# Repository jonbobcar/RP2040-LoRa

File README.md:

# RP2040 LoRa
 RP2040 based board with a LoRa radio

KiCad files are made with KiCad v7.

Care should be used when purchasing BMS to choose one that will auto-start. There are SKUs of this BMS that will only start if external power is provided and then removed. I have chosen AP9101CAK6-ANTRG1, which is an auto-start version.

This board is mostly tested. Files on `main` should be used with caution, you may need to do some debugging.

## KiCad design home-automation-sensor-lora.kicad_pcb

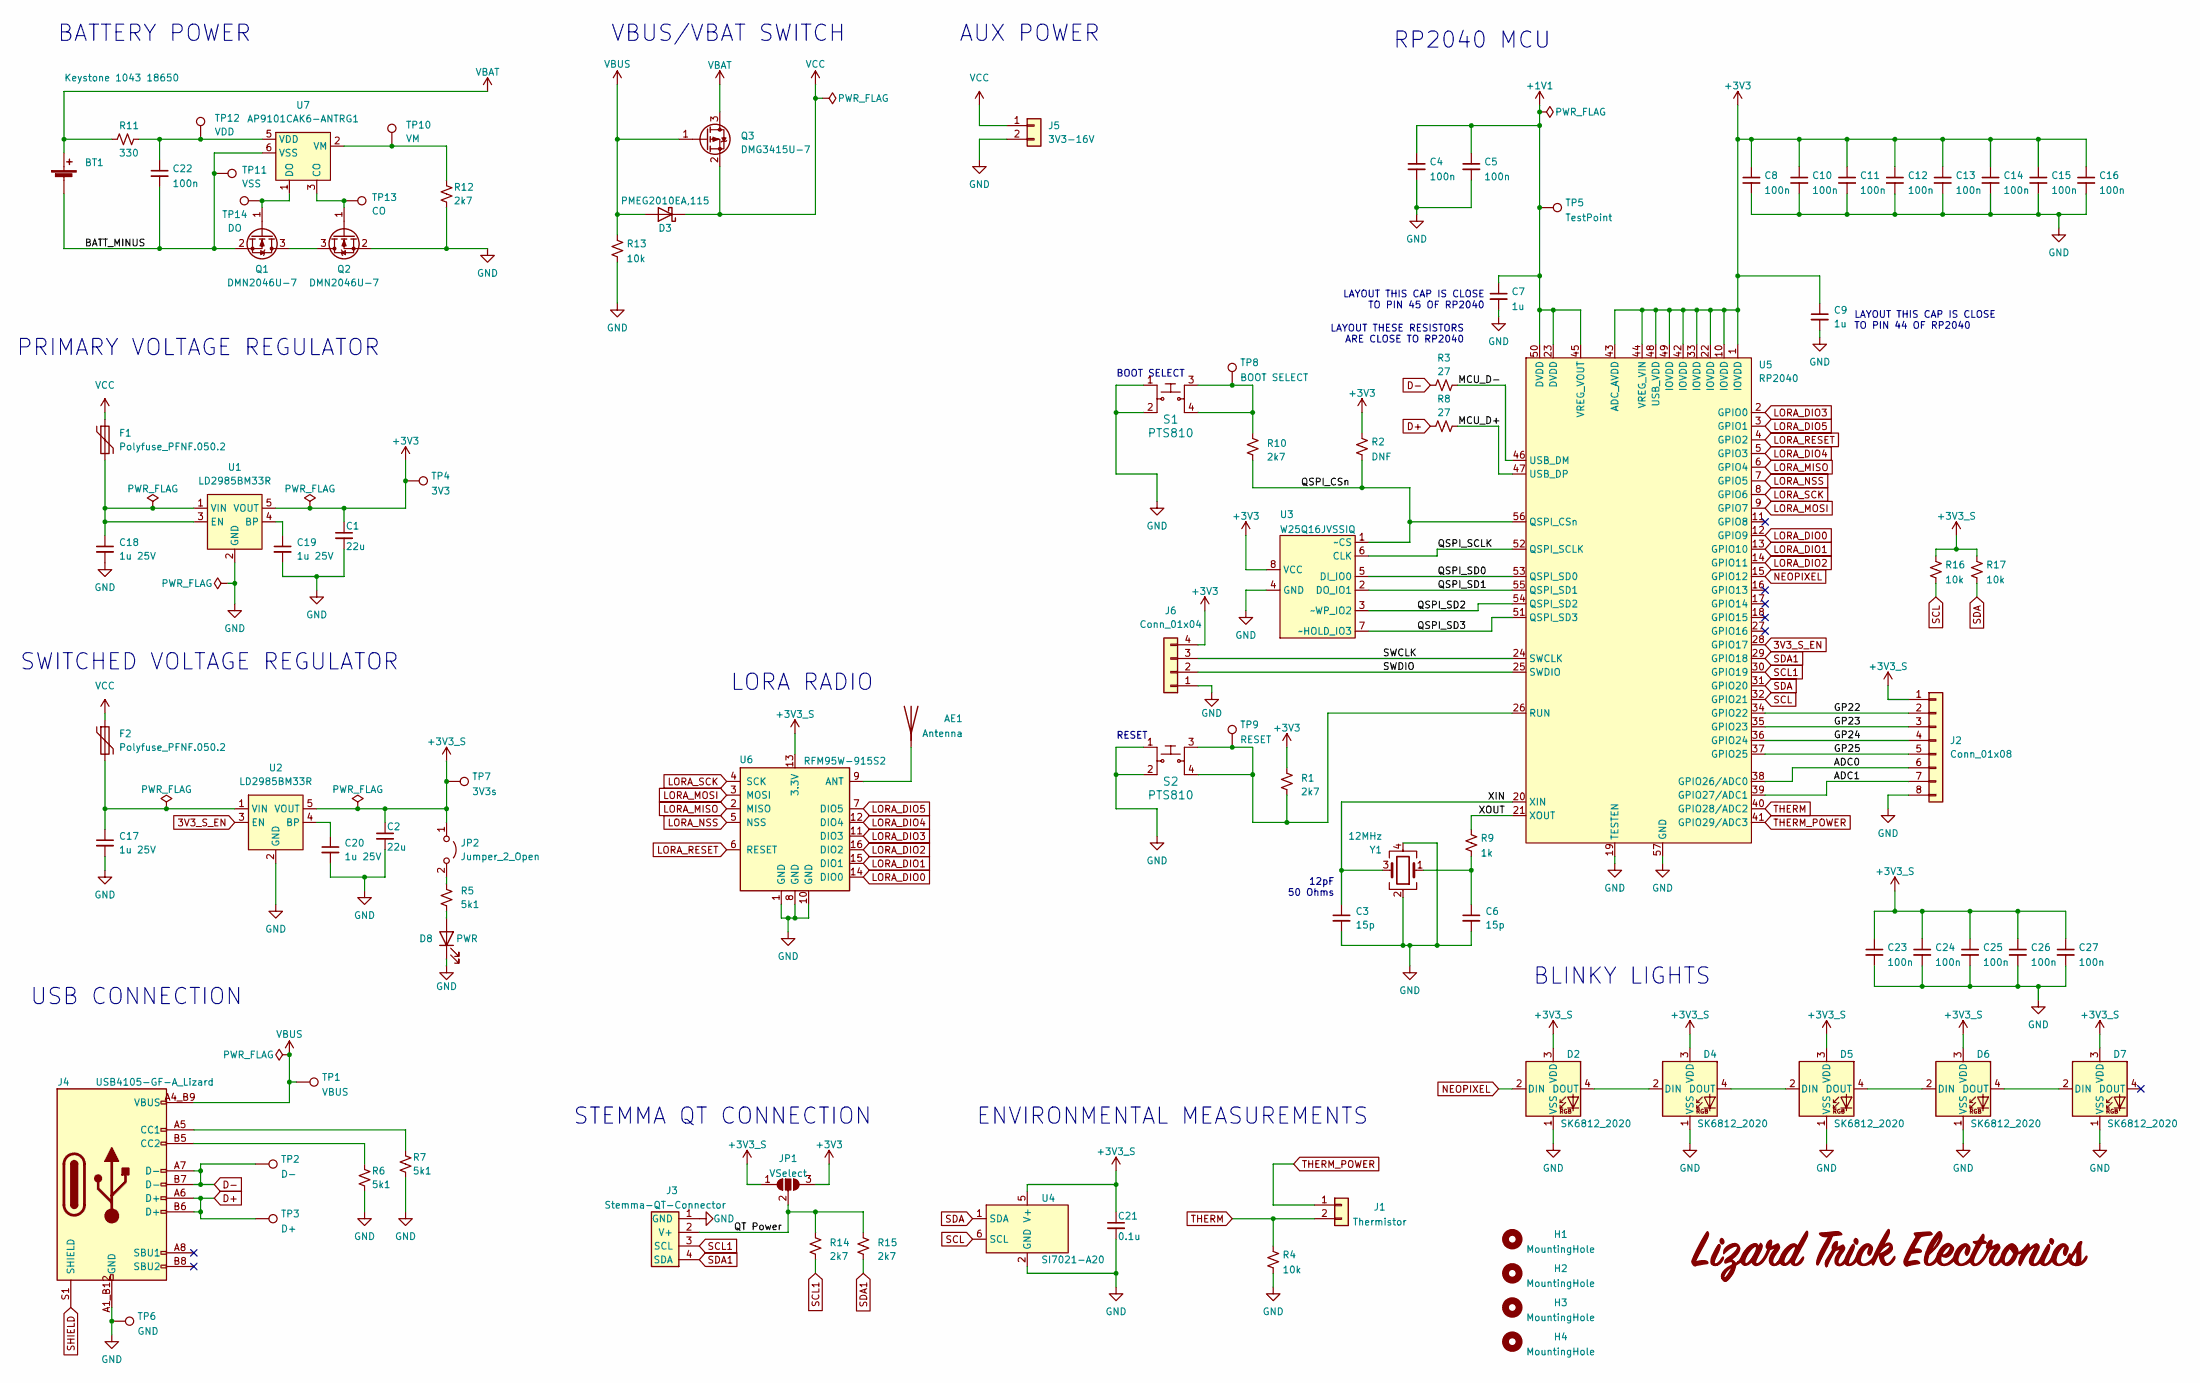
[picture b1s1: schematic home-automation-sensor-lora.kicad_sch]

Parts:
AE1: Antenna; Spring_Antenna_1.0_Drill
BT1: Keystone 1043 18650
C1, C2: 22u; C_0603_Lizard
C3, C6: 15p; C_0603_Lizard
C4, C5, C8, C10, C11, C12, C13, C14, C15, C16, C22, C23, C24, C25, C26, C27: 100n; C_0603_Lizard
C7, C9: 1u; C_0603_Lizard
C17, C18, C19, C20: 1u 25V; C_0603_Lizard
C21: 0.1u; C_0603_Lizard
D2, D4, D5, D6, D7: SK6812_2020; SK6812 2020
D3: PMEG2010EA,115; D_SOD-323
D8: PWR; LED-0805-Lizard
F1, F2: Polyfuse_PFNF.050.2; R_1206_3216Metric
G1: LOGO; Lizard Text Logo
H1, H2, H3, H4: MountingHole; Lizard_MountingHole_3.5mm
J1: Thermistor; PinHeader_1x02_P2.54mm_Vertical
J2: Conn_01x08; Prototype Area 8x8
J3: Stemma-QT-Connector; STEMMA-QT-CONNECTOR
J4: USB4105-GF-A_Lizard; GCT_USB4105-GF-A
J5: 3V3-16V; PinHeader_1x02_P2.54mm_Vertical
J6: Conn_01x04; PinHeader_1x04_P2.54mm_Vertical
JP1: VSelect; SolderJumper-3_P2.0mm_Open_TrianglePad1.0x1.5mm
JP2: Jumper_2_Open; Pin Jumper lizard
Q1, Q2: DMN2046U-7; SOT-23
Q3: DMG3415U-7; SOT-23
R1, R10, R12, R14, R15: 2k7; R_0603_Lizard
R2: DNF; R_0603_Lizard
R3, R8: 27; R_0603_Lizard
R4, R13, R16, R17: 10k; R_0603_Lizard
R5, R6, R7: 5k1; R_0603_Lizard
R9: 1k; R_0603_Lizard
R11: 330; R_0603_Lizard
S1, S2: PTS810; PTS_180_Tactile_Switch
TP1: VBUS; TestPoint_THTPad_1.0x1.0mm_Drill0.5mm
TP2: D-; TestPoint_THTPad_1.0x1.0mm_Drill0.5mm
TP3: D+; TestPoint_THTPad_1.0x1.0mm_Drill0.5mm
TP4: 3V3; TestPoint_THTPad_1.0x1.0mm_Drill0.5mm
TP5: TestPoint; TestPoint_THTPad_1.0x1.0mm_Drill0.5mm
TP6: GND; TestPoint_THTPad_1.0x1.0mm_Drill0.5mm
TP7: 3V3s; TestPoint_THTPad_1.0x1.0mm_Drill0.5mm
TP8: BOOT SELECT; TestPoint_THTPad_1.0x1.0mm_Drill0.5mm
TP9: RESET; TestPoint_THTPad_1.0x1.0mm_Drill0.5mm
TP10: VM; TestPoint_THTPad_1.0x1.0mm_Drill0.5mm-Lizard
TP11: VSS; TestPoint_THTPad_1.0x1.0mm_Drill0.5mm-Lizard
TP12: VDD; TestPoint_THTPad_1.0x1.0mm_Drill0.5mm-Lizard
TP13: CO; TestPoint_THTPad_1.0x1.0mm_Drill0.5mm-Lizard
TP14: DO; TestPoint_THTPad_1.0x1.0mm_Drill0.5mm-Lizard
U1, U2: LD2985BM33R; SOT-23-5
U3: W25Q16JVSSIQ; SOIC-8_5.275x5.275mm_P1.27mm
U4: SI7021-A20
U5: RP2040; RP2040_QFN-56
U6: RFM95W-915S2; XCVR_RFM95W-915S2
U7: AP9101CAK6-ANTRG1; SOT-23-6
Y1: 12MHz; Crystal_SMD_3225-4Pin_3.2x2.5mm

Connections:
3V3_S_EN: U2.3 (EN), U5.28 (GPIO17)
+1V1: C4.1, C5.1, C7.1, TP5.1, U5.23 (DVDD), U5.45 (VREG_VOUT), U5.50 (DVDD)
+3V3: C1.1, C8.1, C9.1, C10.1, C11.1, C12.1, C13.1, C14.1, C15.1, C16.1, J6.4, JP1.3 (B), R1.1, R2.1, TP4.1, U1.5 (VOUT), U3.8 (VCC), U5.1 (IOVDD), U5.10 (IOVDD), U5.22 (IOVDD), U5.33 (IOVDD), U5.42 (IOVDD), U5.43 (ADC_AVDD), U5.44 (VREG_VIN), U5.48 (USB_VDD), U5.49 (IOVDD)
+3V3_S: C2.1, C21.1, C23.1, C24.1, C25.1, C26.1, C27.1, D2.3 (VDD), D4.3 (VDD), D5.3 (VDD), D6.3 (VDD), D7.3 (VDD), J2.1, JP1.1 (A), JP2.1 (A), R16.1, R17.1, TP7.1, U2.5 (VOUT), U4.5 (V+), U6.13 (3.3V)
/ADC0: J2.6, U5.38 (GPIO26/ADC0)
/ADC1: J2.7, U5.39 (GPIO27/ADC1)
/BATT_MINUS: BT1.1 (-), C22.2, Q1.2 (S), TP11.1, U7.6 (VSS)
/GP22: J2.2, U5.34 (GPIO22)
/GP23: J2.3, U5.35 (GPIO23)
/GP24: J2.4, U5.36 (GPIO24)
/GP25: J2.5, U5.37 (GPIO25)
/MCU_D+: R8.2, U5.47 (USB_DP)
/MCU_D-: R3.2, U5.46 (USB_DM)
/QSPI_CSn: R2.2, R10.2, U3.1 (~CS), U5.56 (QSPI_CSn)
/QSPI_SCLK: U3.6 (CLK), U5.52 (QSPI_SCLK)
/QSPI_SD0: U3.5 (DI_IO0), U5.53 (QSPI_SD0)
/QSPI_SD1: U3.2 (DO_IO1), U5.55 (QSPI_SD1)
/QSPI_SD2: U3.3 (~WP_IO2), U5.54 (QSPI_SD2)
/QSPI_SD3: U3.7 (~HOLD_IO3), U5.51 (QSPI_SD3)
/QT Power: J3.2 (V+), JP1.2 (C), R14.1, R15.1
/SWCLK: J6.3, U5.24 (SWCLK)
/SWDIO: J6.2, U5.25 (SWDIO)
/XIN: C3.1, U5.20 (XIN), Y1.3
/XOUT: R9.1, U5.21 (XOUT)
D+: J4.A6 (D+), J4.B6 (D+), R8.1, TP3.1
D-: J4.A7 (D-), J4.B7 (D-), R3.1, TP2.1
GND: C1.2, C2.2, C3.2, C4.2, C5.2, C6.2, C7.2, C8.2, C9.2, C10.2, C11.2, C12.2, C13.2, C14.2, C15.2, C16.2, C17.2, C18.2, C19.2, C20.2, C21.2, C23.2, C24.2, C25.2, C26.2, C27.2, D2.1 (VSS), D4.1 (VSS), D5.1 (VSS), D6.1 (VSS), D7.1 (VSS), D8.1 (K), J2.8, J3.1 (GND), J4.A1_B12 (GND), J4.B1_A12 (GND), J5.2, J6.1, Q2.2 (S), R4.2, R6.2, R7.2, R12.2, R13.2, S1.1, S1.2, S2.1, S2.2, TP6.1, U1.2 (GND), U2.2 (GND), U3.4 (GND), U4.2 (GND), U5.19 (TESTEN), U5.57 (GND), U6.1 (GND), U6.8 (GND), U6.10 (GND), Y1.2, Y1.4
LORA_DIO0: U5.12 (GPIO9), U6.14 (DIO0)
LORA_DIO1: U5.13 (GPIO10), U6.15 (DIO1)
LORA_DIO2: U5.14 (GPIO11), U6.16 (DIO2)
LORA_DIO3: U5.2 (GPIO0), U6.11 (DIO3)
LORA_DIO4: U5.5 (GPIO3), U6.12 (DIO4)
LORA_DIO5: U5.3 (GPIO1), U6.7 (DIO5)
LORA_MISO: U5.6 (GPIO4), U6.2 (MISO)
LORA_MOSI: U5.9 (GPIO7), U6.3 (MOSI)
LORA_NSS: U5.7 (GPIO5), U6.5 (NSS)
LORA_RESET: U5.4 (GPIO2), U6.6 (RESET)
LORA_SCK: U5.8 (GPIO6), U6.4 (SCK)
NEOPIXEL: D2.2 (DIN), U5.15 (GPIO12)
unnamed: AE1.1 (A), U6.9 (ANT)
unnamed: C6.1, R9.2, Y1.1
unnamed: D2.4 (DOUT), D4.2 (DIN)
unnamed: D4.4 (DOUT), D5.2 (DIN)
unnamed: D5.4 (DOUT), D6.2 (DIN)
unnamed: D6.4 (DOUT), D7.2 (DIN)
unnamed: D8.2 (A), R5.2
unnamed: J4.A5 (CC1), R7.1
unnamed: J4.B5 (CC2), R6.1
unnamed: JP2.2 (B), R5.1
unnamed: Q1.3 (D), Q2.3 (D)
unnamed: Q1.1 (G), TP14.1, U7.1 (DO)
unnamed: Q2.1 (G), TP13.1, U7.3 (CO)
unnamed: R10.1, S1.3, S1.4, TP8.1
unnamed: C19.1, U1.4 (BP)
unnamed: C18.1, F1.2, U1.1 (VIN), U1.3 (EN)
unnamed: C20.1, U2.4 (BP)
unnamed: C17.1, F2.2, U2.1 (VIN)
unnamed: R1.2, S2.3, S2.4, TP9.1, U5.26 (RUN)
unnamed: C22.1, R11.1, TP12.1, U7.5 (VDD)
unnamed: R12.1, TP10.1, U7.2 (VM)
SCL: R16.2, U4.6 (SCL), U5.32 (GPIO21)
SCL1: J3.3 (SCL), R14.2, U5.30 (GPIO19)
SDA: R17.2, U4.1 (SDA), U5.31 (GPIO20)
SDA1: J3.4 (SDA), R15.2, U5.29 (GPIO18)
SHIELD: J4.S1 (SHIELD)
THERM: J1.2, R4.1, U5.40 (GPIO28/ADC2)
THERM_POWER: J1.1, U5.41 (GPIO29/ADC3)
VBUS: D3.2 (A), J4.A4_B9 (VBUS), J4.B4_A9 (VBUS), Q3.1 (G), R13.1, TP1.1
VCC: D3.1 (K), F1.1, F2.1, J5.1, Q3.2 (S)
VDD: BT1.2 (+), Q3.3 (D), R11.2

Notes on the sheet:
STEMMA QT CONNECTION
RESET
RP2040 MCU
LAYOUT THIS CAP IS CLOSE TO PIN 44 OF RP2040
12pF 50 Ohms
USB CONNECTION
LORA RADIO
AUX POWER
SWITCHED VOLTAGE REGULATOR
VBUS/VBAT SWITCH
LAYOUT THESE RESISTORS ARE CLOSE TO RP2040
LAYOUT THIS CAP IS CLOSE TO PIN 45 OF RP2040
BLINKY LIGHTS
BATTERY POWER
PRIMARY VOLTAGE REGULATOR
ENVIRONMENTAL MEASUREMENTS
BOOT SELECT

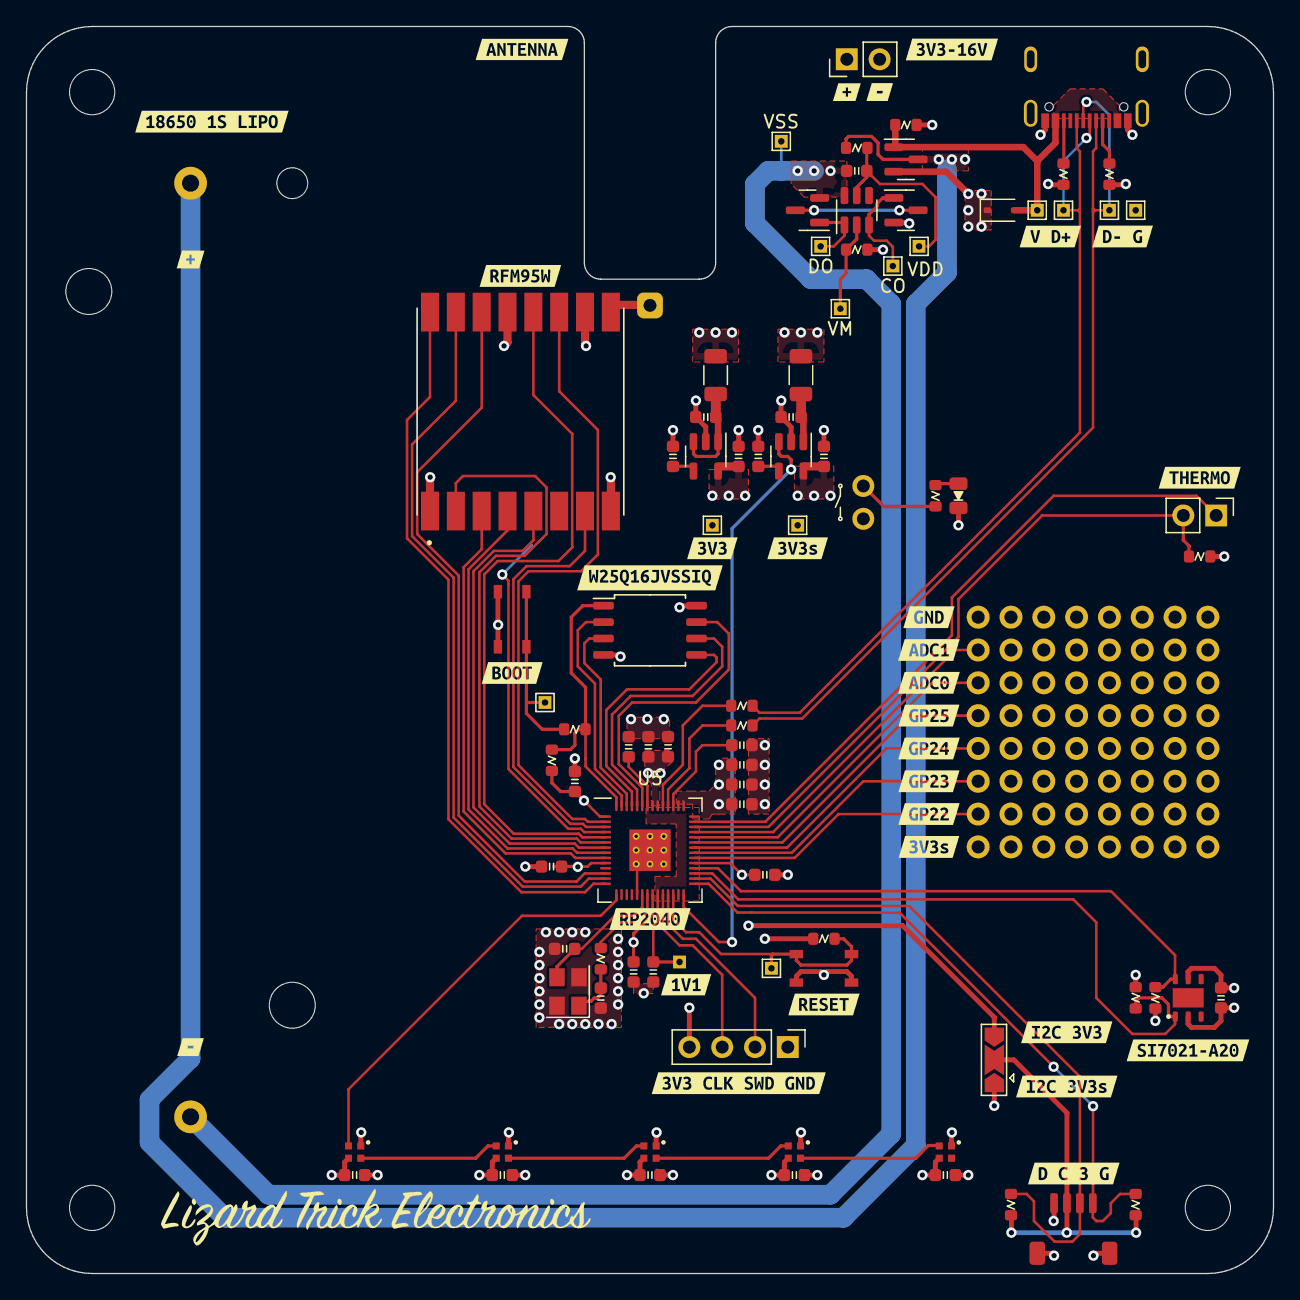
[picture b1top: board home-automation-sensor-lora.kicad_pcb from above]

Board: 4 copper layers, 96.5 x 96.5 mm, 126 parts (1 on the bottom side), 69 nets.

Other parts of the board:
kibuzzard-63ABB0D8: G***; kibuzzard-63ABB0D8
kibuzzard-63ABB2C2: G***; kibuzzard-63ABB2C2
kibuzzard-63ABB2DA: G***; kibuzzard-63ABB2DA
kibuzzard-63ABB9BF: G***; kibuzzard-63ABB9BF
kibuzzard-63ABB33A: G***; kibuzzard-63ABB33A
kibuzzard-63ABB90E: G***; kibuzzard-63ABB90E
kibuzzard-63ABB100: G***; kibuzzard-63ABB100
kibuzzard-63ABB154: G***; kibuzzard-63ABB154
kibuzzard-63ABB174: G***; kibuzzard-63ABB174
kibuzzard-63ABB255: G***; kibuzzard-63ABB255
kibuzzard-63ABB925: G***; kibuzzard-63ABB925
kibuzzard-63ABBA8A, kibuzzard-63ABBA8A#2: G***; kibuzzard-63ABBA8A
kibuzzard-63ABBAAB, kibuzzard-63ABBAAB#2: G***; kibuzzard-63ABBAAB
kibuzzard-63ABCCDB: G***; kibuzzard-63ABCCDB
kibuzzard-63ABCCE2: G***; kibuzzard-63ABCCE2
kibuzzard-63ABCCEA: G***; kibuzzard-63ABCCEA
kibuzzard-63ABCCF2: G***; kibuzzard-63ABCCF2
kibuzzard-63ABCCF8: G***; kibuzzard-63ABCCF8
kibuzzard-63ABCCFF: G***; kibuzzard-63ABCCFF
kibuzzard-63ABCD0C: G***; kibuzzard-63ABCD0C
kibuzzard-63ABCD05: G***; kibuzzard-63ABCD05
kibuzzard-63ABCD13: G***; kibuzzard-63ABCD13
kibuzzard-63ABD5CF: G***; kibuzzard-63ABD5CF
kibuzzard-63ABD432: G***; kibuzzard-63ABD432
kibuzzard-63ABD482: G***; kibuzzard-63ABD482
kibuzzard-63ABD564: G***; kibuzzard-63ABD564
kibuzzard-63B9C3A5: G***; kibuzzard-63B9C3A5
kibuzzard-63B27CA9: G***; kibuzzard-63B27CA9
kibuzzard-63B32B21: G***; kibuzzard-63B32B21

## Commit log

2023-02-11 Initial commit of files
2023-02-11 Updated RP2040 footprint and updated routing to accommodate it
2023-02-12 Added test points to BMS chip.
    Tested BMS functionality and it is not working. It will prevent the battery from being charged at a high voltage, but it will not allow the battery to discharge under normal conditions. Interestingly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
2023-02-12 update git ignore
2023-02-12 added board photo
2023-02-12 Adjusted power planes around BMS
2023-02-13 finalized gerbers for production
2023-02-23 Moved LORA_MISO to GPIO4 and LORA_RESET to GPIO2
2023-02-25 updated git ignore
2023-02-26 exported updated step file
2023-02-26 updated silkscreen and footprints
2023-02-26 corrected mirrored stemma qt connector pinout
2023-02-26 updated resistor values
2023-02-26 fixed routing to lora module
2023-02-26 updated BMS to auto-start version
